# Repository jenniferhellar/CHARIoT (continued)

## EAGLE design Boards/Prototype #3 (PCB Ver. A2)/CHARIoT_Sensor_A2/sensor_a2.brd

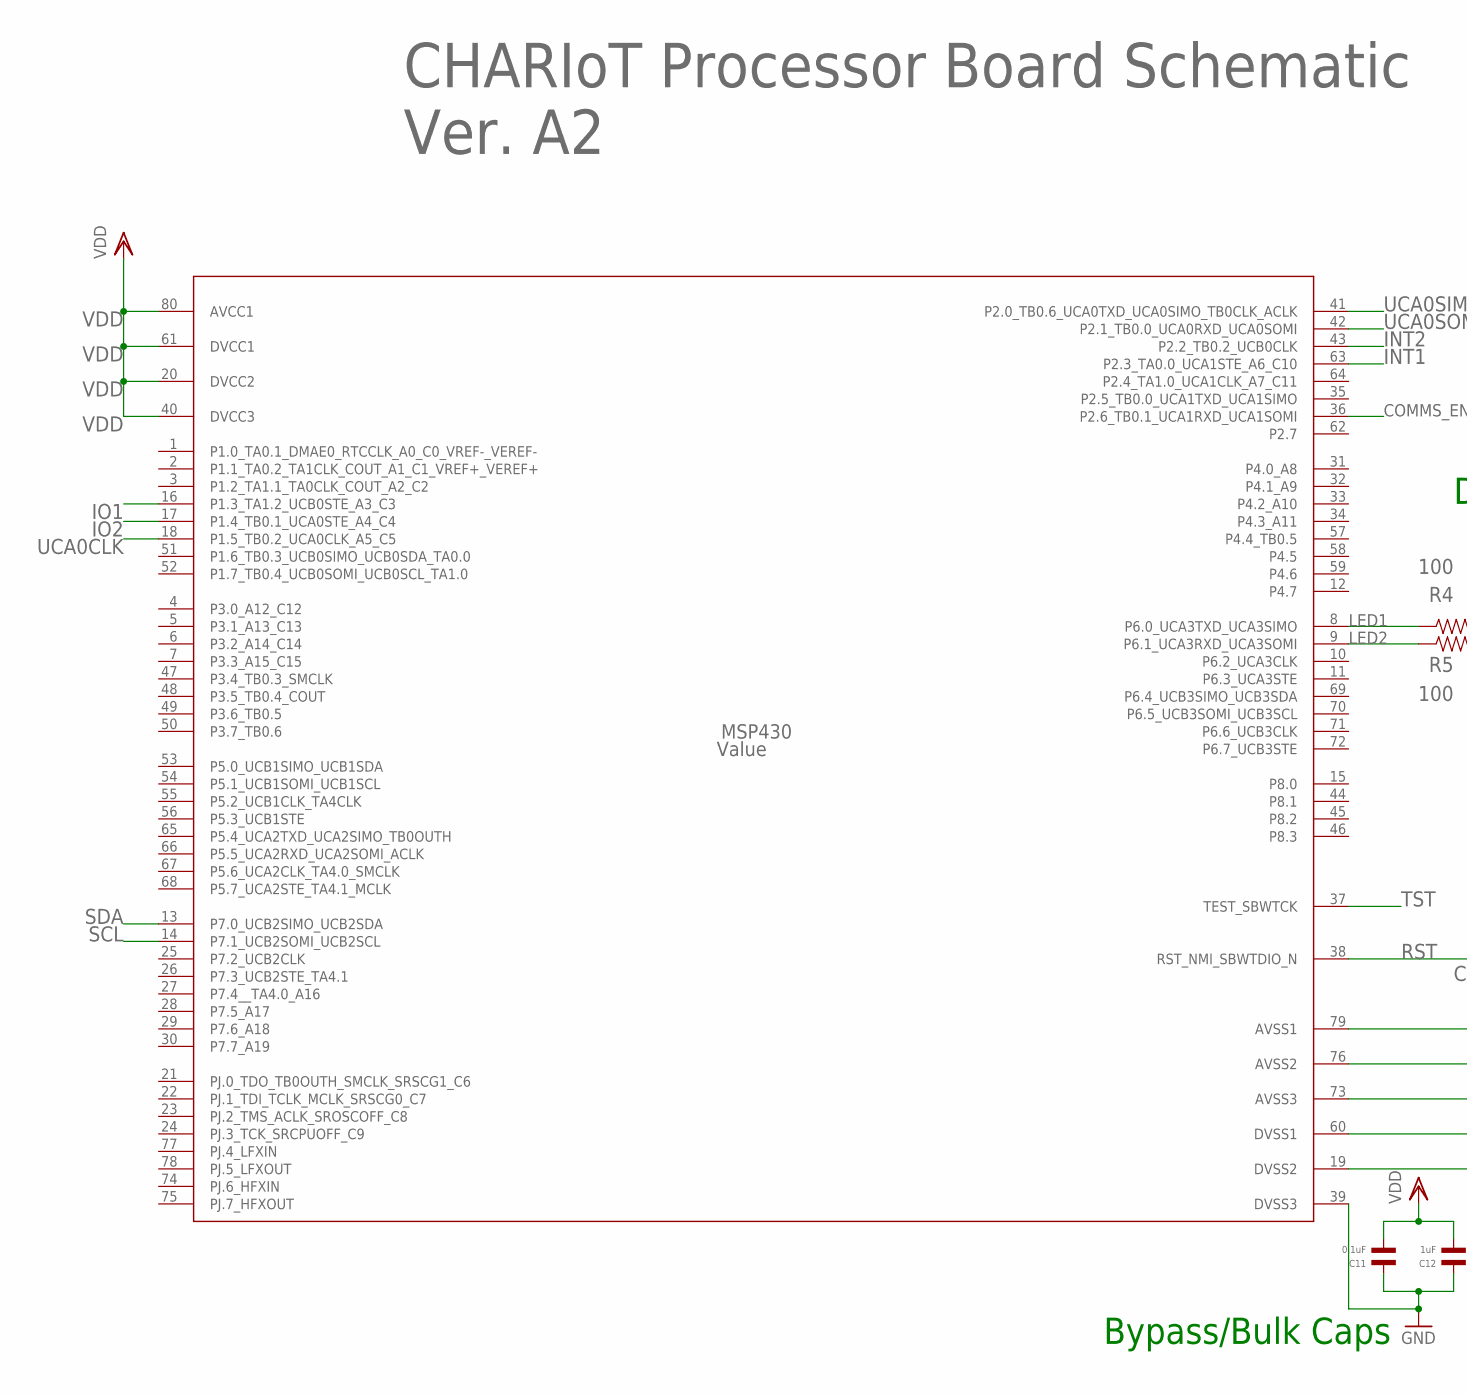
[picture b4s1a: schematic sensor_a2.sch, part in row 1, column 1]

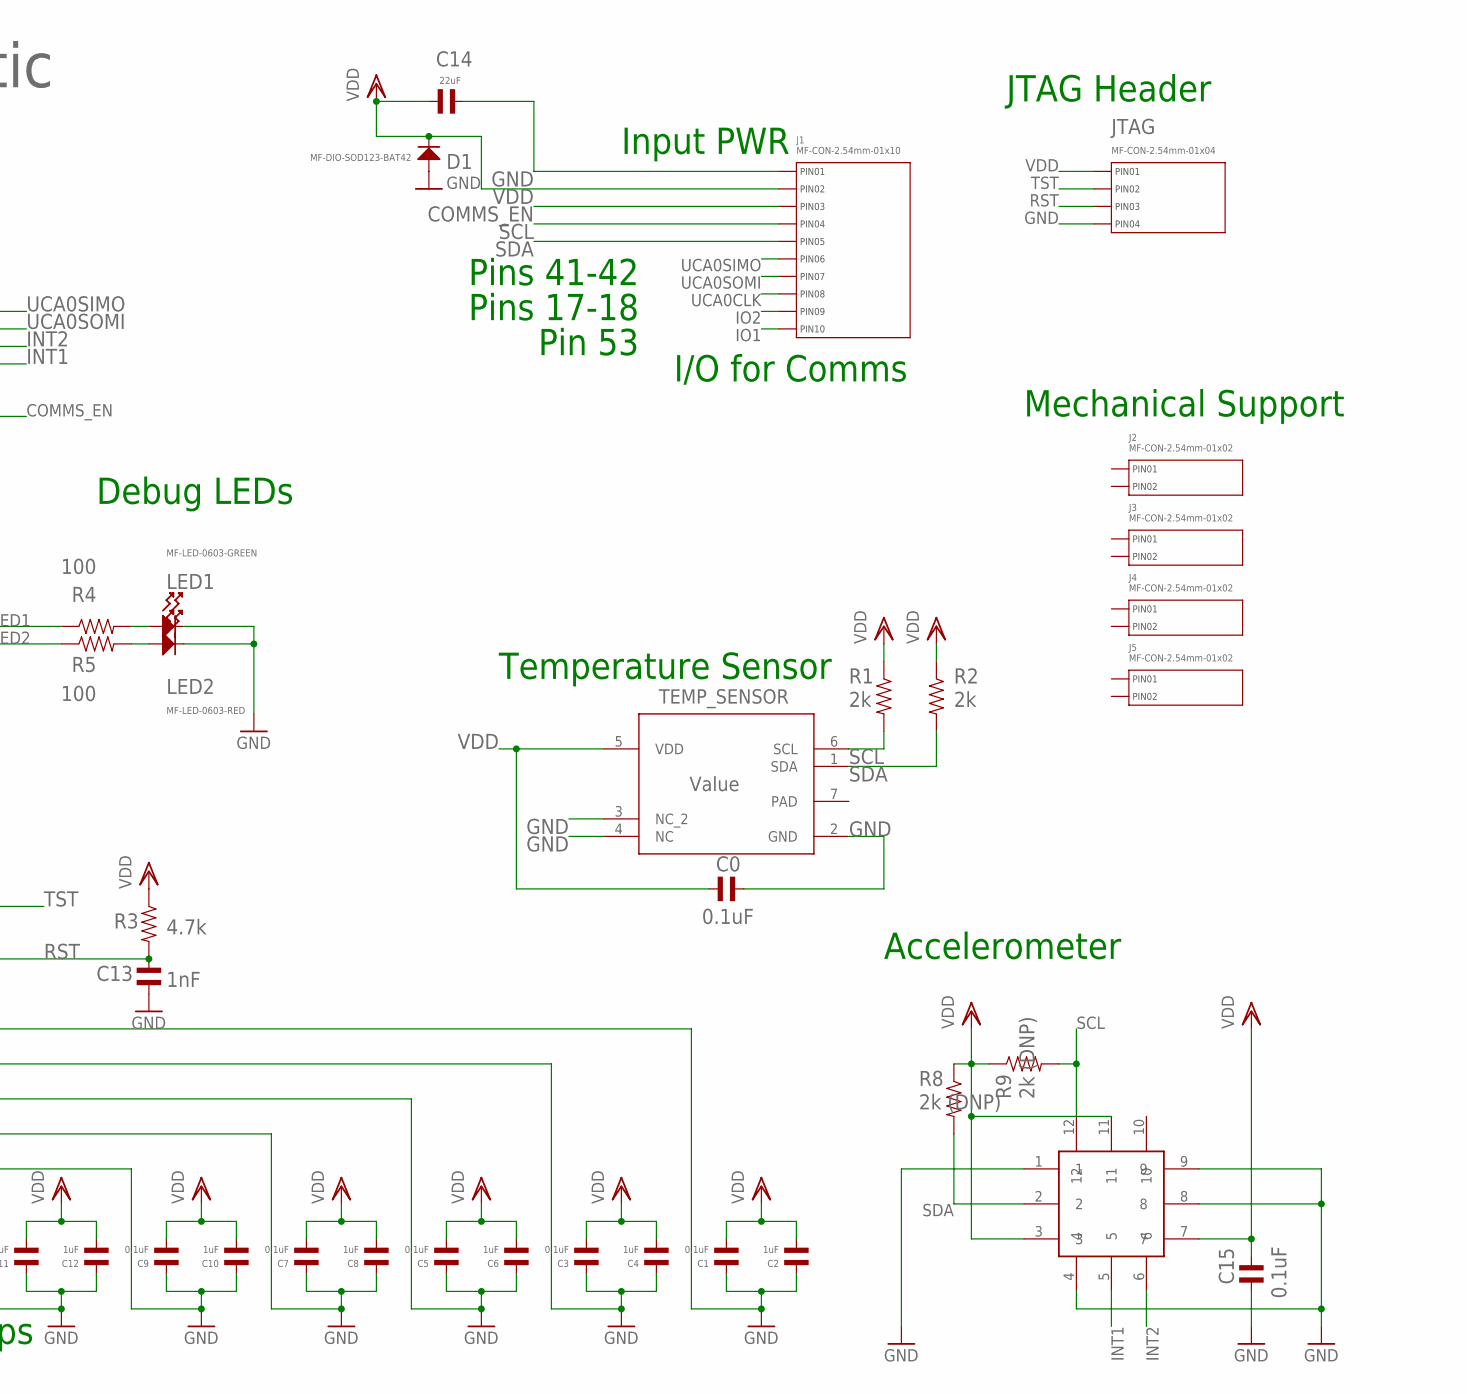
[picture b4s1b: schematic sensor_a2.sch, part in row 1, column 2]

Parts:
ACCEL: BMA253; LGA-12
C0, C1, C3, C5, C7, C9, C11, C15: 0.1uF; C0603
C2, C4, C6, C8, C10, C12: 1uF; C0603
C13: 1nF; C0603
C14: 22uF; C0603
D1: MF-DIO-SOD123-BAT42; SOD-123
J1: MF-CON-2.54mm-01x10; PTH_2.54MM_01X10
J2, J3, J4, J5: MF-CON-2.54mm-01x02; PTH_2.54MM_01X02
JTAG: MF-CON-2.54mm-01x04; PTH_2.54MM_01X04
LED1: MF-LED-0603-GREEN; LED0603
LED2: MF-LED-0603-RED; LED0603
MSP430: Value; PN0080A_N
R1, R2: 2k; R0603
R3: 4.7k; R0603
R4, R5: 100; R0603
R8, R9: 2k (DNP); R0603
TEMP_SENSOR: Value; DMB0006A

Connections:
COMMS_EN: J1.P$3 (PIN3), MSP430.36 (P2.6_TB0.1_UCA1RXD_UCA1SOMI)
GND: ACCEL.1, ACCEL.4, ACCEL.8, ACCEL.9, C0.P$2, C1.P$1, C2.P$1, C3.P$1, C4.P$1, C5.P$1, C6.P$1, C7.P$1, C8.P$1, C9.P$1, C10.P$1, C11.P$1, C12.P$1, C13.P$2, C14.P$2, C15.P$1, D1.ANODE, J1.P$1 (PIN1), JTAG.P$4 (PIN4), LED1.CATHODE, LED2.CATHODE, MSP430.19 (DVSS2), MSP430.39 (DVSS3), MSP430.60 (DVSS1), MSP430.73 (AVSS3), MSP430.76 (AVSS2), MSP430.79 (AVSS1), TEMP_SENSOR.2 (GND), TEMP_SENSOR.3 (NC_2), TEMP_SENSOR.4 (NC)
INT1: ACCEL.5, MSP430.63 (P2.3_TA0.0_UCA1STE_A6_C10)
INT2: ACCEL.6, MSP430.43 (P2.2_TB0.2_UCB0CLK)
IO1: J1.P$10 (PIN10), MSP430.16 (P1.3_TA1.2_UCB0STE_A3_C3)
IO2: J1.P$9 (PIN9), MSP430.17 (P1.4_TB0.1_UCA0STE_A4_C4)
LED1: MSP430.8 (P6.0_UCA3TXD_UCA3SIMO), R4.P$1
LED2: MSP430.9 (P6.1_UCA3RXD_UCA3SOMI), R5.P$1
unnamed: LED1.ANODE, R4.P$2
unnamed: LED2.ANODE, R5.P$2
PAD: TEMP_SENSOR.7 (PAD)
RST: C13.P$1, JTAG.P$3 (PIN3), MSP430.38 (RST_NMI_SBWTDIO_N), R3.P$2
SCL: ACCEL.12, J1.P$4 (PIN4), MSP430.14 (P7.1_UCB2SOMI_UCB2SCL), R1.P$2, R9.P$2, TEMP_SENSOR.6 (SCL)
SDA: ACCEL.2, J1.P$5 (PIN5), MSP430.13 (P7.0_UCB2SIMO_UCB2SDA), R2.P$2, R8.P$2, TEMP_SENSOR.1 (SDA)
TST: JTAG.P$2 (PIN2), MSP430.37 (TEST_SBWTCK)
UCA0CLK: J1.P$8 (PIN8), MSP430.18 (P1.5_TB0.2_UCA0CLK_A5_C5)
UCA0SIMO: J1.P$6 (PIN6), MSP430.41 (P2.0_TB0.6_UCA0TXD_UCA0SIMO_TB0CLK_ACLK)
UCA0SOMI: J1.P$7 (PIN7), MSP430.42 (P2.1_TB0.0_UCA0RXD_UCA0SOMI)
VDD: ACCEL.3, ACCEL.7, ACCEL.11, C0.P$1, C1.P$2, C2.P$2, C3.P$2, C4.P$2, C5.P$2, C6.P$2, C7.P$2, C8.P$2, C9.P$2, C10.P$2, C11.P$2, C12.P$2, C14.P$1, C15.P$2, D1.CATHODE, J1.P$2 (PIN2), JTAG.P$1 (PIN1), MSP430.20 (DVCC2), MSP430.40 (DVCC3), MSP430.61 (DVCC1), MSP430.80 (AVCC1), R1.P$1, R2.P$1, R3.P$1, R8.P$1, R9.P$1, TEMP_SENSOR.5 (VDD)

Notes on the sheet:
Pins 17-18
Pin 53
Pins 41-42
Input PWR
Temperature Sensor
JTAG Header
Debug LEDs
Bypass/Bulk Caps
I/O for Comms
CHARIoT Processor Board Schematic Ver. A2
Accelerometer
Mechanical Support

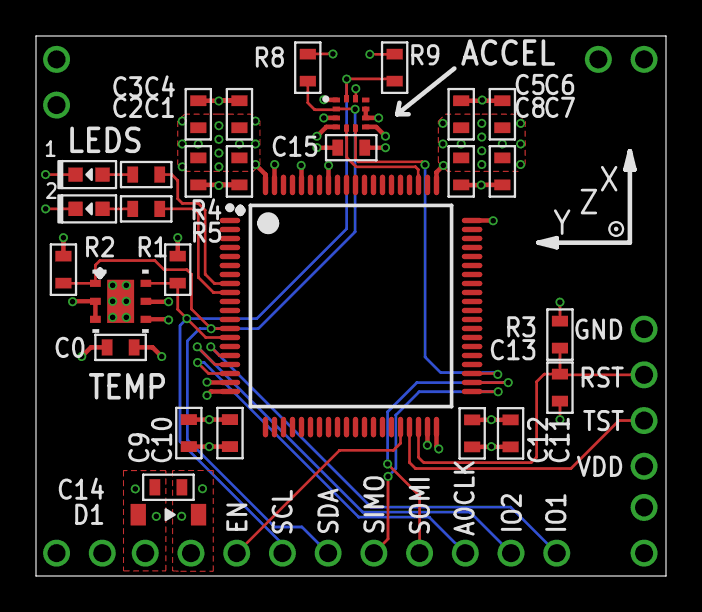
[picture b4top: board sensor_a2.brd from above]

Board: 4 copper layers, 35.0 x 30.0 mm, 36 parts (0 on the bottom side), 18 nets.

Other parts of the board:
U$1: XYZ-LABEL

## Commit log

2020-01-18 Datasheets
2020-01-18 Board designs
2020-01-18 Code
2020-01-18 Documenation (posters, presentations, etc.)
2020-11-08 Added additional documentation, summary presentation, meeting notes
2020-11-09 Created a README.md
